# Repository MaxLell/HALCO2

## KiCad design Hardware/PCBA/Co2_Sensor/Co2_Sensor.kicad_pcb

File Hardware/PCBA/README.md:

## Changes in the PCBA
The PCBA contains some minor errors, which are indicated here. If you want to reproduce the PCBA, please make sure: 
- to reverse the polarity of C5. The (-) indicator on the Silkscreen is placed on the wrong pad. Please check the Nets in the PCBA File. The (-)-Pin of C5 needs to be connected to GND.
- to keep R3 unsoldered. This constantly pulls down the BOOT Pin of the Microcontroller.

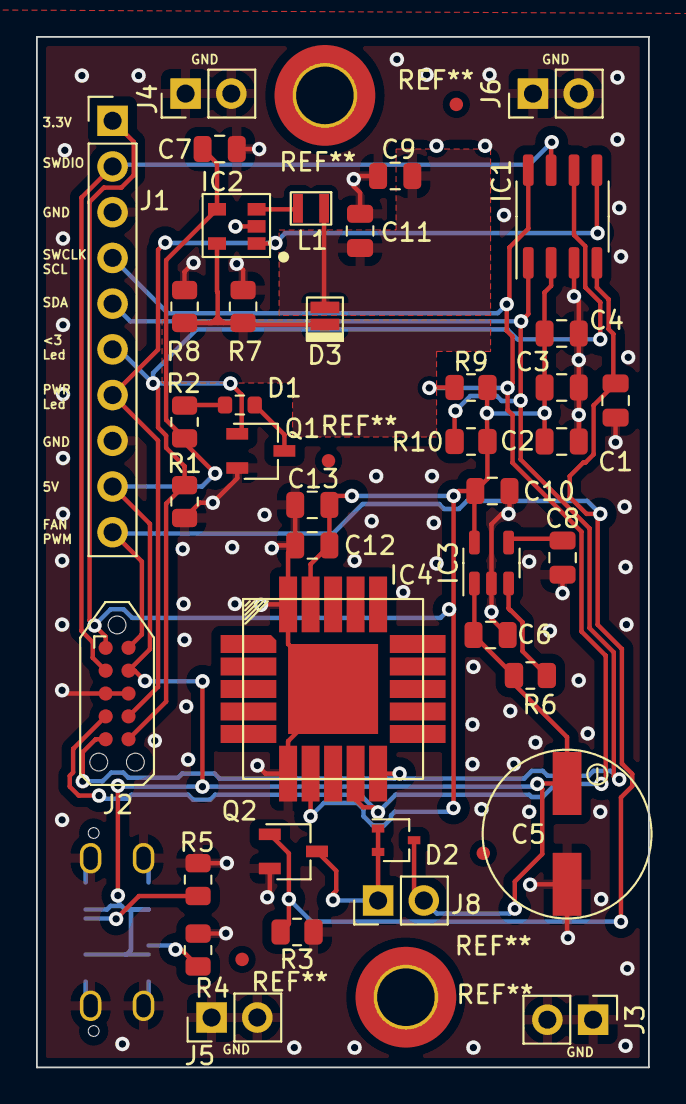
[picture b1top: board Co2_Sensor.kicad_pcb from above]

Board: 2 copper layers, 34.0 x 57.2 mm, 41 parts (1 on the bottom side), 19 nets.

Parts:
C1, C4, C8, C11, C13: 100n; C_0805_2012Metric
C2, C7, C9: 10u; C_0805_2012Metric
C3, C6, C10, C12: 1u; C_0805_2012Metric
C5: 330u; Cap_Elko_330u_6V3
D1: R_0603_1608Metric
D2: DAN235FMT106; SOT-323_SC-70
D3: LED; Cree_SMD2
IC1: STM32G031J6; SO-8_3.9x4.9mm_P1.27mm
IC2: PAM2804; TSOT25
IC3: LDK120M33R; TSOT-23-5
IC4: SCD4X
J1: Conn_01x10_Male; PinHeader_1x10_P2.54mm_Vertical
J2: Conn_01x10; Tag-Connect_TC2050-IDC-NL_2x05_P1.27mm_Vertical
J3, J4, J5, J6, J8: PinHeader_1x02_P2.54mm_Vertical
J7: USB_C_Receptacle_JAE_DX07S024WJ3R400
L1: 4u7; SRP2010DPA-4R7M
Q1, Q2: Q_NMOS_GSD; TSOT-23
R1, R3, R4, R5, R6, R9, R10: 5k1; R_0805_2012Metric
R2: 270R; R_0805_2012Metric
R7: 6R8; R_0805_2012Metric
R8: 5R6; R_0805_2012Metric

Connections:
+3V3: C2.1, C3.1, C4.1, C10.1, C12.1, C13.1, IC1.2 (VDD), IC3.5 (VOUT), IC4.7 (VDD), IC4.19 (VDDH), J1.1, J2.1, R9.1, R10.1
+5V: C5.1, C6.1, C7.1, D2.3 (Kathode), IC2.4 (VIN), IC3.1 (VIN), J1.9, J2.9, J7.A4 (VBUS), J7.A9 (VBUS), J7.B4 (VBUS), J7.B9 (VBUS), J8.2, R2.1, R6.2
/Power_LedDriver_Fan/Power LED Anode: C9.1, C11.1, D3.2 (A), L1.2
/Power_LedDriver_Fan/Power LED Kathode: D3.1 (K), IC2.5 (FB), R7.1, R8.1
DcFan_TTL: C1.1, IC1.4 (PA0/PA1/PA2/PF2-NRST), J1.10, J2.10, Q2.1 (G), R3.1
GND: C1.2, C2.2, C3.2, C4.2, C5.2, C6.2, C7.2, C8.2, C9.2, C10.2, C11.2, C12.2, C13.2, IC1.3 (GND), IC2.2 (GND), IC3.2 (GND), IC4.6 (GND), IC4.20 (GND), IC4.21 (GND), J1.3, J1.8, J2.3, J2.8, J3.1, J3.2, J4.1, J4.2, J5.1, J5.2, J6.1, J6.2, J7.A1 (GND), J7.A12 (GND), J7.B1 (GND), J7.B12 (GND), J7.S1 (SHIELD), Q1.2 (S), Q2.2 (S), R1.2, R3.2, R4.2, R5.2, R7.2, R8.2
I2C_SCL: IC1.8 (PB5/PB6/PA14-BOOT0/PA15), IC4.9 (SCL), J1.4, J2.4, R9.2
I2C_SDA: IC1.1 (PB7/PB8/PB9/PC14-OSC32_IN), IC4.10 (SDA), J1.5, J2.5, R10.2
unnamed: C8.1, IC3.4 (BYP/ADJ/NC)
unnamed: D1.1 (K), Q1.3 (D)
unnamed: D1.2 (A), R2.2
unnamed: D2.1 (Anode), D2.2 (Anode), J8.1, Q2.3 (D)
unnamed: IC2.3 (SW), L1.1
unnamed: IC3.3 (EN), R6.1
unnamed: J7.A5 (CC1), R5.1
unnamed: J7.B5 (CC2), R4.1
SWDIO: IC1.7 (PA13), J1.2, J2.2
SignalLed_PWM: IC1.5 (PA8/PA11[PA9]/PB0/PB1), IC2.1 (EN), J1.7, J2.7
StatusLed_TTL: IC1.6 (PA12[PA10]), J1.6, J2.6, Q1.1 (G), R1.1

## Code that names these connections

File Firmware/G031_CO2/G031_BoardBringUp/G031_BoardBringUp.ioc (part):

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Mcu.Name=STM32G031J(4-6)Mx
Mcu.Package=SO8N
Mcu.UserName=STM32G031J6Mx
PA0.Signal=S_TIM2_CH1_ETR
PA11\ [PA9].GPIOParameters=GPIO_Label
PA11\ [PA9].GPIO_Label=EyeLED
PA11\ [PA9].Signal=GPIO_Output
PA12\ [PA10].GPIOParameters=GPIO_Label
PA12\ [PA10].GPIO_Label=BlinkyLED
PA12\ [PA10].Signal=GPIO_Output
PA14-BOOT0__PA15__PB5__PB6.StandardMode=true
PB0__PB1__PA8__PA11\ [PA9].StandardMode=true
PC14-OSC32_IN\ (PC14).GPIOParameters=GPIO_Label
PC14-OSC32_IN\ (PC14).GPIO_Label=TestPIN3
PC14-OSC32_IN\ (PC14).Signal=GPIO_Output
PC14-OSC32_IN\ (PC14)__PB7__PB8__PB9.StandardMode=true
PF2\ -\ NRST__PA0__PA1__PA2.StandardMode=true
RCC.HSE_VALUE=8000000
RCC.SYSCLKFreq_VALUE=16000000
board=custom

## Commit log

2022-09-27 Working Prototype
    - Created a tested PCBA
    - Created the Firmware including major clean up
    - Added a BoardBringUp Project, to test out the system
    - Added photos for documentation purposes
2022-09-27 Project Setup Instructions
    - Added Bug fix details for the PCBA fabrication
    - Added Board-Bring-Up Instructions for the Firmware flashing process
2022-10-02 Add Hardware Files
    Added a Hardware Component BOM
    Added the 3D print files for HALCO2
2022-10-04 Added a 4th mode, where the Fan and the PowerLed are switched off; Code Refactoring
    - Added a 4th mode, which will be active during times, when the window is open (so during the night and during the day - this reduces the power consumption significantly and it should also increase t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
    - Refactored the code:
    - Created a new module for the fan
    - Move the logic, which was previously all stacked in the main into dedicated functions.
2022-10-04 Update the spine, to make it more durable; Improve the airflow through the housing so that it all passes the CO2 Sensor
2023-08-06 Minor refactoring
2023-11-05 Added an averaging filter; Removed Experimental Data from Repo (JS Code for Hysterese)
2023-11-05 Added Ceeding to the project, refactored the Airquality procedures out into their own module
2023-11-05 Changed the animation for the worst air quality to be less annoying; resolved a minor bug fix - off-by-one-error
